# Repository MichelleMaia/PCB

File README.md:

# PCB
# PCB Layout Design

**Author:** Michelle Cavalcanti Maia  

This repository showcases a collection of PCB layout designs along with their respective circuit schematics.  
All projects were created using **KiCad** as part of the course [KiCad Like a Pro 3E](https://www.udemy.com/course/kicad-like-a-pro-3e).

## Projects
- **LED Torch** – a simple lighting circuit
- **Breadboard Power Supply** – regulated power supply for prototyping
- **Tiny Solar Power Supply** – compact solar-powered circuit
- **MCU Datalogger** – microcontroller-based data logging system

## Tools
- **KiCad** – open-source PCB design software

## About
I am passionate about embedded systems, electronics, and PCB design.  
For more projects and articles, visit my website: [michellemaia.com](https://www.michellemaia.com)

---

📅 *Last updated: September 2025*

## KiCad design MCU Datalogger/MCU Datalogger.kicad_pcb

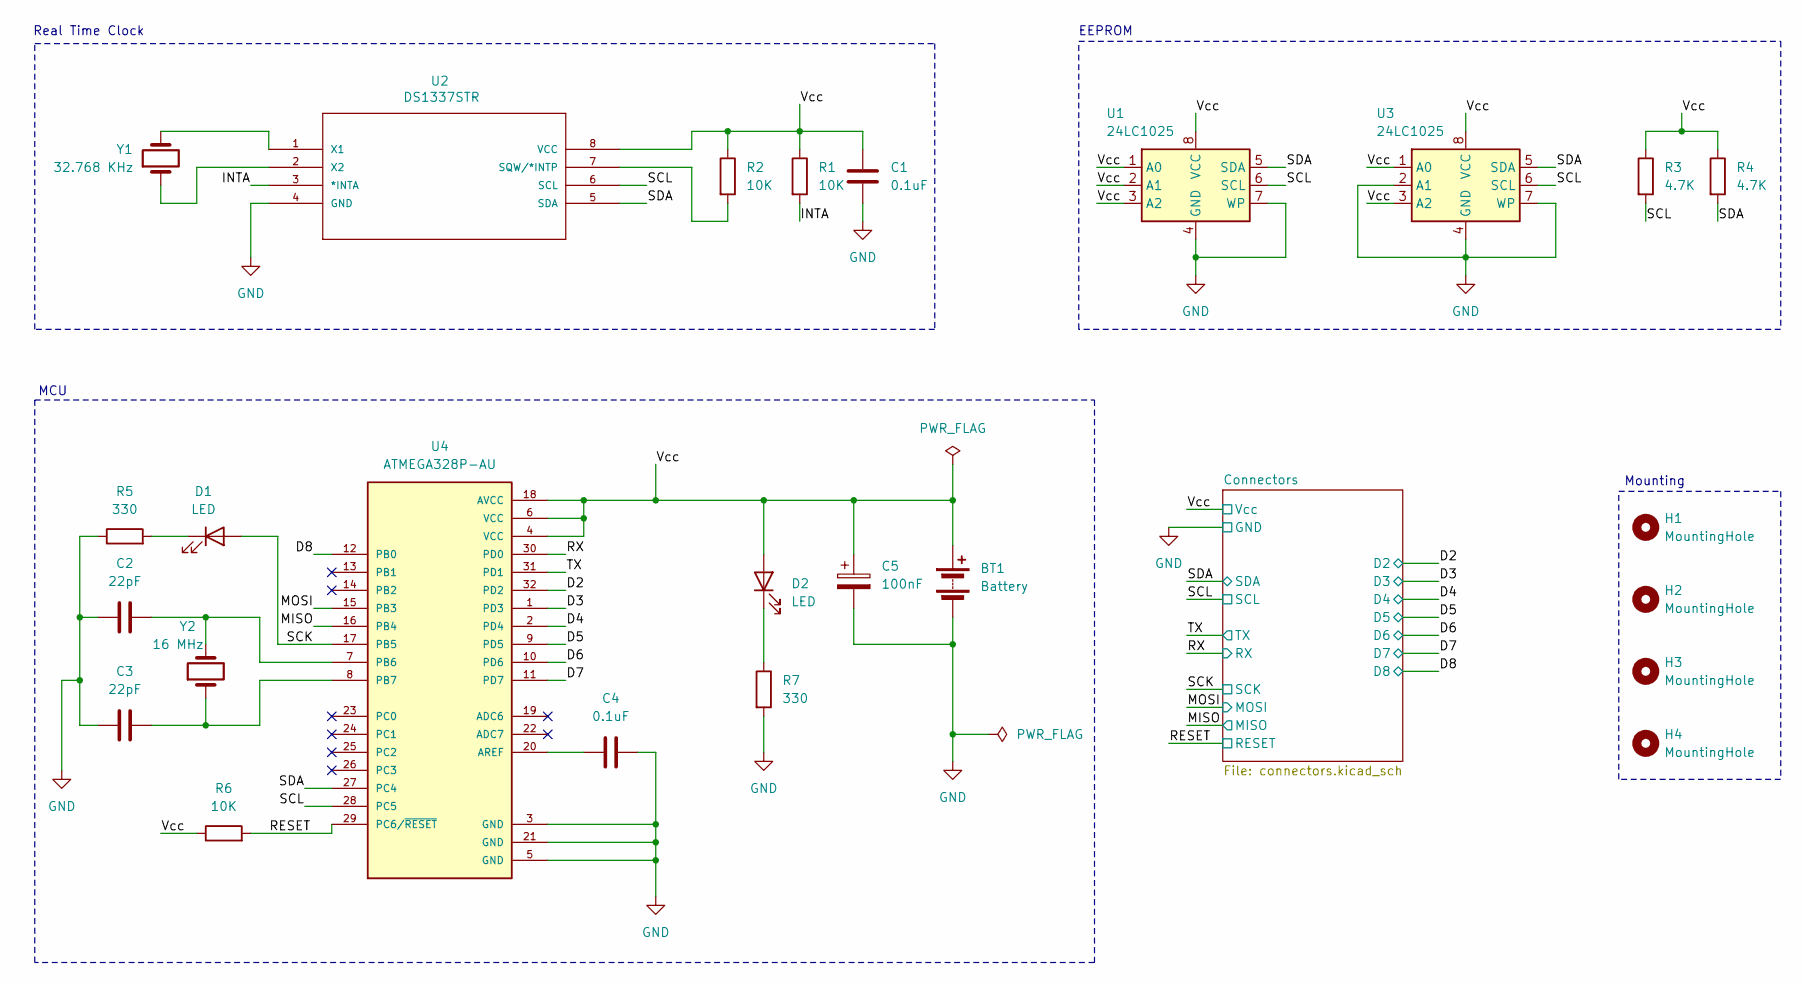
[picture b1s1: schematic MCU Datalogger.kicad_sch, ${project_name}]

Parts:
BT1: Battery; PinHeader_1x02_P2.54mm_Vertical
C1, C4: 0.1uF; C_0805_2012Metric
C2, C3: 22pF; C_0805_2012Metric
C5: 100nF; C_0805_2012Metric
D1, D2: LED; LED_0805_2012Metric
H1, H2, H3, H4: MountingHole; MountingHole_2.1mm
R1, R2, R6: 10K; R_0805_2012Metric
R3, R4: 4.7K; R_0805_2012Metric
R5, R7: 330; R_0805_2012Metric
U1, U3: 24LC1025; SOIC-8_W5.3mm
U2: DS1337STR; 21-0041B_8; MANUFACTURER_PART_NUMBER DS1337S+T&R
U4: ATMEGA328P-AU; QFP80P900X900X120-32N; PARTREV 8271A
Y1: 32.768 KHz; Crystal_SMD_5032-2Pin_5.0x3.2mm_HandSoldering
Y2: 16 MHz; Crystal_SMD_5032-2Pin_5.0x3.2mm_HandSoldering

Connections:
/D2: U4.32 (PD2); also elsewhere on the board
/D3: U4.1 (PD3); also elsewhere on the board
/D4: U4.2 (PD4); also elsewhere on the board
/D5: U4.9 (PD5); also elsewhere on the board
/D6: U4.10 (PD6); also elsewhere on the board
/D7: U4.11 (PD7); also elsewhere on the board
/D8: U4.12 (PB0); also elsewhere on the board
/INTA: R1.2, U2.3 (*INTA)
/MISO: U4.16 (PB4); also elsewhere on the board
/MOSI: U4.15 (PB3); also elsewhere on the board
/RESET: R6.2, U4.29 (PC6/~RESET); also elsewhere on the board
/RX: U4.30 (PD0); also elsewhere on the board
/SCK: D1.2 (A), U4.17 (PB5); also elsewhere on the board
/SCL: R3.2, U1.6 (SCL), U2.6 (SCL), U3.6 (SCL), U4.28 (PC5); also elsewhere on the board
/SDA: R4.2, U1.5 (SDA), U2.5 (SDA), U3.5 (SDA), U4.27 (PC4); also elsewhere on the board
/TX: U4.31 (PD1); also elsewhere on the board
/Vcc: BT1.1 (+), C1.1, C5.1, D2.2 (A), R1.1, R2.1, R3.1, R4.1, R6.1, U1.1 (A0), U1.2 (A1), U1.3 (A2), U1.8 (VCC), U2.8 (VCC), U3.1 (A0), U3.3 (A2), U3.8 (VCC), U4.4 (VCC), U4.6 (VCC), U4.18 (AVCC); also elsewhere on the board
GND: BT1.2 (-), C1.2, C2.1, C3.1, C4.2, C5.2, R5.1, R7.2, U1.4 (GND), U1.7 (WP), U2.4 (GND), U3.2 (A1), U3.4 (GND), U3.7 (WP), U4.3 (GND), U4.5 (GND), U4.21 (GND); also elsewhere on the board
unnamed: D1.1 (K), R5.2
unnamed: D2.1 (K), R7.1
unnamed: R2.2, U2.7 (SQW/*INTP)
unnamed: U2.1 (X1), Y1.2
unnamed: U2.2 (X2), Y1.1
unnamed: C4.1, U4.20 (AREF)
unnamed: C2.2, U4.7 (PB6), Y2.2
unnamed: C3.2, U4.8 (PB7), Y2.1

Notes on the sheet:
Real Time Clock
Mounting
EEPROM
MCU

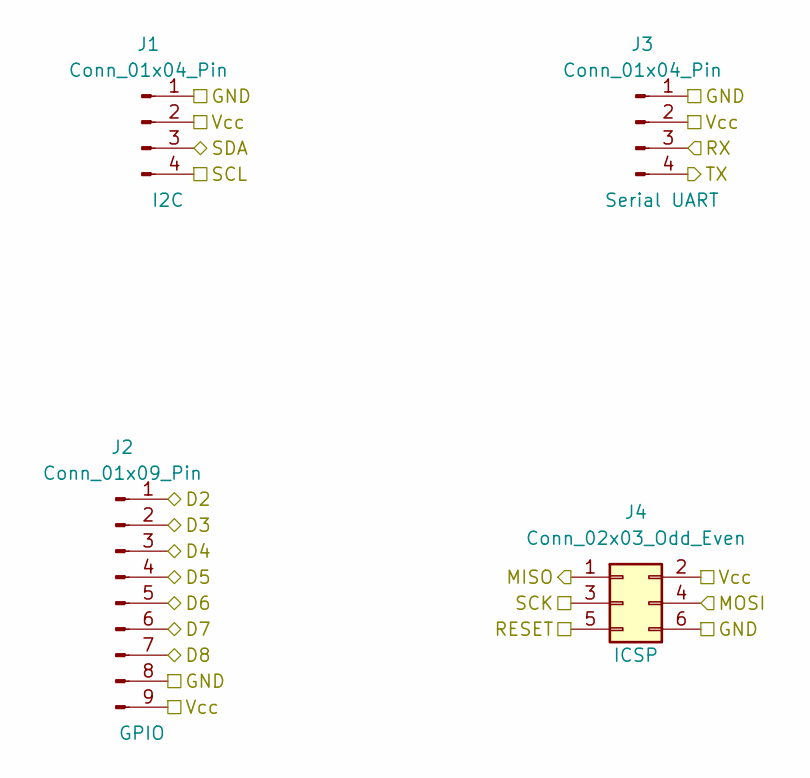
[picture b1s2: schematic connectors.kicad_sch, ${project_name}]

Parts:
J1, J3: Conn_01x04_Pin; PinHeader_1x04_P2.54mm_Vertical
J2: Conn_01x09_Pin; PinHeader_1x09_P2.54mm_Vertical
J4: Conn_02x03_Odd_Even; PinHeader_2x03_P2.54mm_Vertical

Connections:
/D2: J2.1; also elsewhere on the board
/D3: J2.2; also elsewhere on the board
/D4: J2.3; also elsewhere on the board
/D5: J2.4; also elsewhere on the board
/D6: J2.5; also elsewhere on the board
/D7: J2.6; also elsewhere on the board
/D8: J2.7; also elsewhere on the board
/MISO: J4.1; also elsewhere on the board
/MOSI: J4.4; also elsewhere on the board
/RESET: J4.5; also elsewhere on the board
/RX: J3.3; also elsewhere on the board
/SCK: J4.3; also elsewhere on the board
/SCL: J1.4; also elsewhere on the board
/SDA: J1.3; also elsewhere on the board
/TX: J3.4; also elsewhere on the board
/Vcc: J1.2, J2.9, J3.2, J4.2; also elsewhere on the board
GND: J1.1, J2.8, J3.1, J4.6; also elsewhere on the board

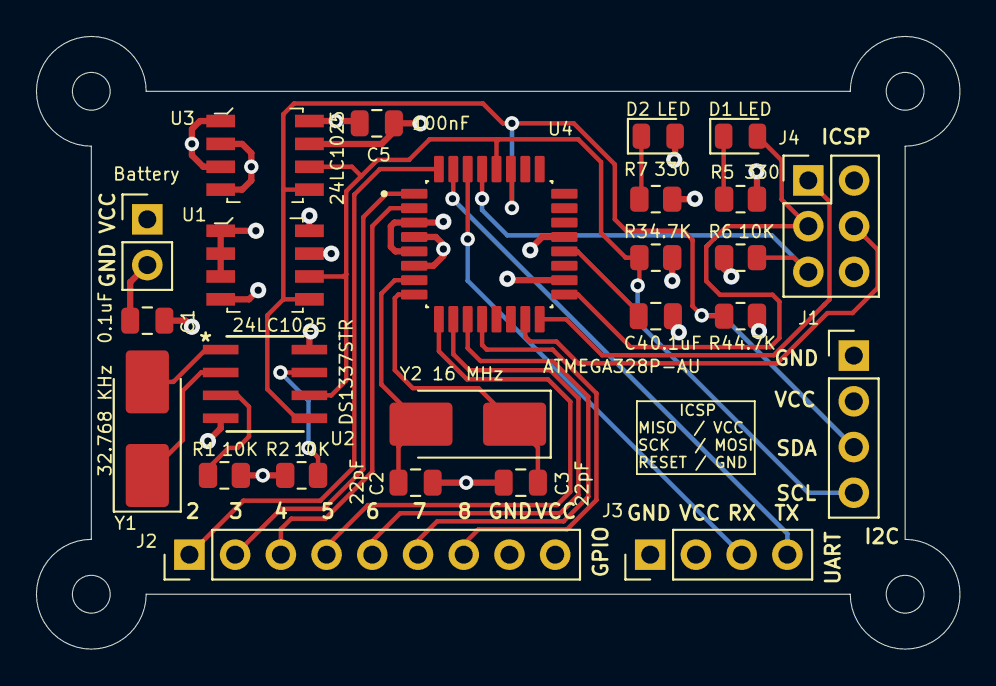
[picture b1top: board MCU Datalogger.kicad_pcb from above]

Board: 4 copper layers, 51.3 x 34.0 mm, 29 parts (0 on the bottom side), 26 nets.

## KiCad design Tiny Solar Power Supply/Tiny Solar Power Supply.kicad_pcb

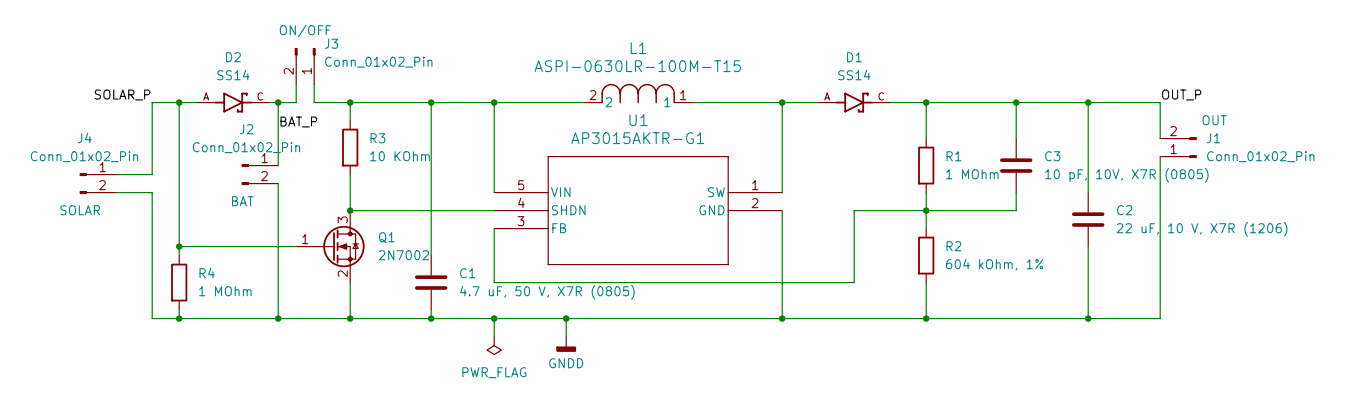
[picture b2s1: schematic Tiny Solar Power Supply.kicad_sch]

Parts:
C1: 4.7 uF, 50 V, X7R (0805); C_0805_2012Metric
C2: 22 uF, 10 V, X7R (1206); C_1206_3216Metric
C3: 10 pF, 10V, X7R (0805); C_0805_2012Metric
D1, D2: SS14; DIOM4325X250N; PARTREV O2102
J1, J2, J3: Conn_01x02_Pin; PinHeader_1x02_P2.54mm_Vertical
J4: Conn_01x02_Pin; PinHeader_1x02_P2.54mm_Horizontal
L1: ASPI-0630LR-100M-T15; IND_ASPI-0630LR_ABR
Q1: 2N7002; SOT-23
R1, R4: 1 MOhm; R_0805_2012Metric
R2: 604 kOhm, 1%; R_0805_2012Metric
R3: 10 KOhm; R_0805_2012Metric
U1: AP3015AKTR-G1; SOT23-5_1P55X2P9_DIO

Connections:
/BAT_P: D2.C, J2.1, J3.2
/OUT_P: C2.1, C3.1, D1.C, J1.2, R1.1
/SOLAR_P: D2.A, J4.1, Q1.1 (G), R4.1
GNDD: C1.2, C2.2, J1.1, J2.2, J4.2, Q1.2 (S), R2.2, R4.2, U1.2 (GND)
unnamed: C1.1, J3.1, L1.2, R3.1, U1.5 (VIN)
unnamed: Q1.3 (D), R3.2, U1.4 (SHDN)
unnamed: C3.2, R1.2, R2.1, U1.3 (FB)
unnamed: D1.A, L1.1, U1.1 (SW)

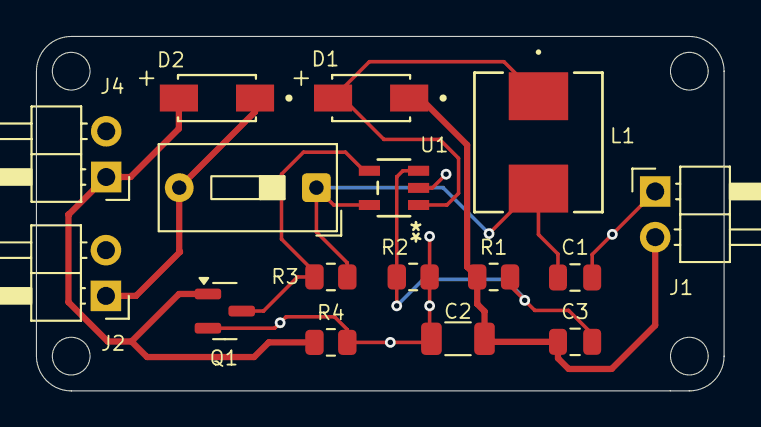
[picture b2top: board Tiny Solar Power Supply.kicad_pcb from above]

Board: 2 copper layers, 38.2 x 19.7 mm, 16 parts (0 on the bottom side), 8 nets.

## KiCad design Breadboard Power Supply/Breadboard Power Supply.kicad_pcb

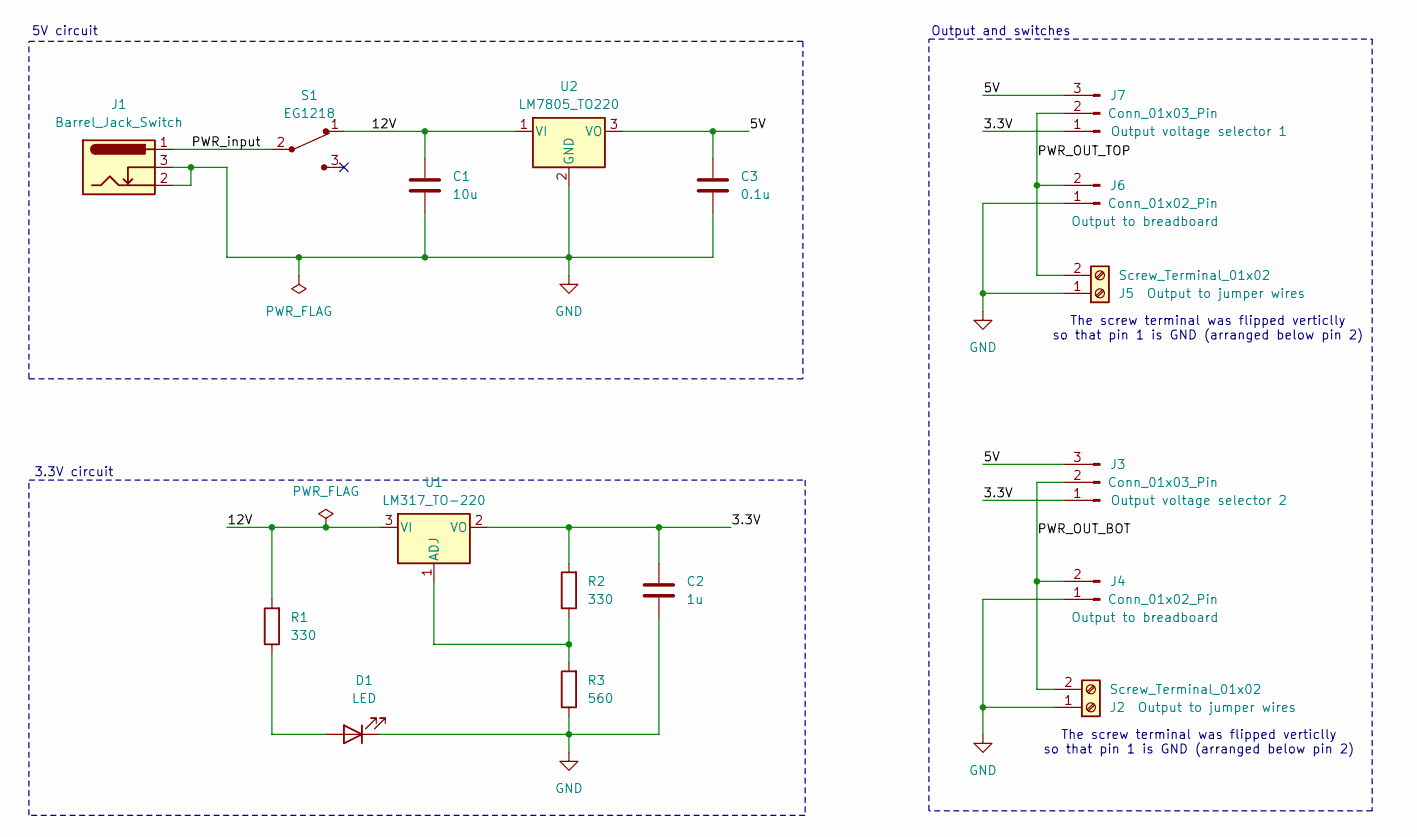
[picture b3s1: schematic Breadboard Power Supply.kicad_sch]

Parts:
C1: 10u; C_Disc_D3.0mm_W1.6mm_P2.50mm
C2: 1u; C_Disc_D3.0mm_W1.6mm_P2.50mm
C3: 0.1u; C_Disc_D3.0mm_W1.6mm_P2.50mm
D1: LED; LED_D5.0mm
J1: Barrel_Jack_Switch; BarrelJack_Horizontal
J2, J5: Screw_Terminal_01x02; TerminalBlock_bornier-2_P5.08mm
J3, J7: Conn_01x03_Pin; PinHeader_1x03_P2.54mm_Vertical
J4, J6: Conn_01x02_Pin; PinHeader_1x02_P2.54mm_Vertical
R1, R2: 330; R_Axial_DIN0204_L3.6mm_D1.6mm_P7.62mm_Horizontal
R3: 560; R_Axial_DIN0204_L3.6mm_D1.6mm_P7.62mm_Horizontal
S1: EG1218; Switch_Slide_11.6x4mm_EG1218; MPN EG1218; Digi-Key_PN EG1903-ND
U1: LM317_TO-220; TO-220-3_Vertical
U2: LM7805_TO220; TO-220-3_Vertical

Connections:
/3.3V: C2.1, J3.1, J7.1, R2.2, U1.2 (VO)
/5V: C3.1, J3.3, J7.3, U2.3 (VO)
/12V: C1.1, R1.2, S1.1, U1.3 (VI), U2.1 (VI)
/PWR_OUT_BOT: J2.2, J3.2, J4.2
/PWR_OUT_TOP: J5.2, J6.2, J7.2
/PWR_input: J1.1, S1.2
GND: C1.2, C2.2, C3.2, D1.1 (K), J1.2, J1.3, J2.1, J4.1, J5.1, J6.1, R3.1, U2.2 (GND)
unnamed: D1.2 (A), R1.1
unnamed: R2.1, R3.2, U1.1 (ADJ)

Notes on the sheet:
3.3V circuit
5V circuit
Output and switches
The screw terminal was flipped verticlly so that pin 1 is GND (arranged below pin 2)

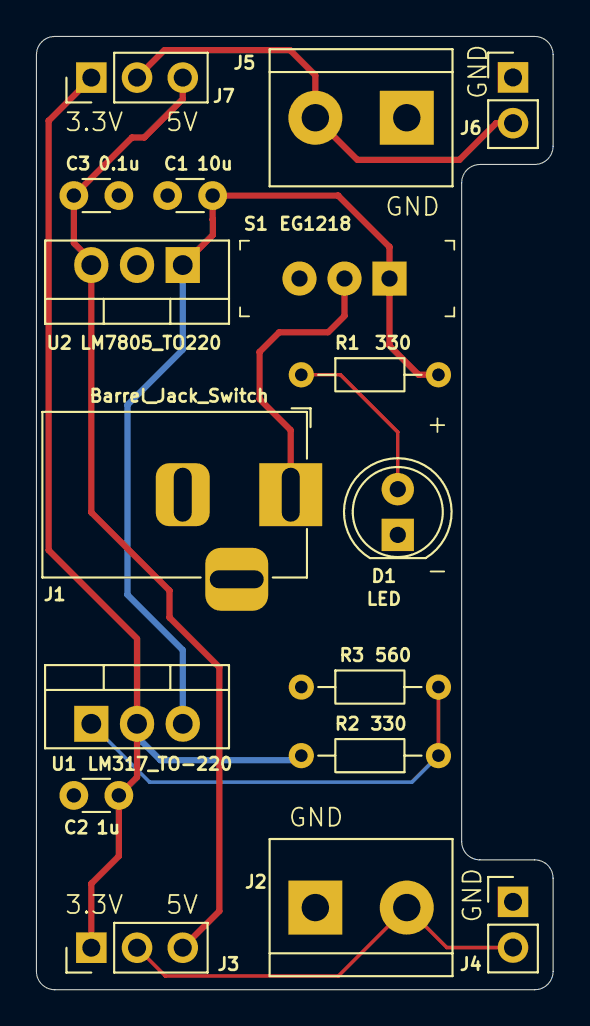
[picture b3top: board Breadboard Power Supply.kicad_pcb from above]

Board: 2 copper layers, 28.7 x 53.0 mm, 17 parts (0 on the bottom side), 9 nets.

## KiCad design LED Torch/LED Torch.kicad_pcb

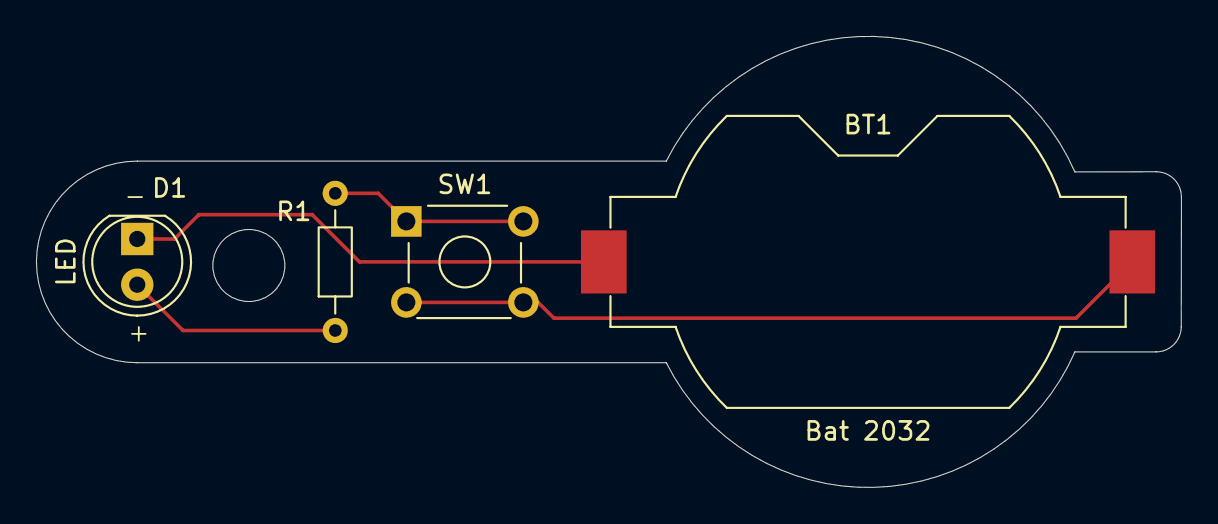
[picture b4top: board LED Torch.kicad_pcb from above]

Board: 2 copper layers, 63.6 x 25.1 mm, 4 parts (0 on the bottom side), 4 nets.

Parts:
BT1: Bat 2032; BatteryHolder_Keystone_1058_1x2032
D1: LED; LED_D5.0mm
R1: R; R_Axial_DIN0204_L3.6mm_D1.6mm_P7.62mm_Horizontal
SW1: SW_DPDT_x2; SW_TH_Tactile_Omron_B3F-10xx

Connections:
/LED_anode: D1.2 (A), R1.1
/LED_cathode: BT1.2 (-), D1.1 (K)
/bat_pos: BT1.1 (+), SW1.2 (B)
unnamed: R1.2, SW1.1 (A)

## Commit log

2025-09-03 Update README.md
    Adding projects descriptions
2025-09-03 LED Torch - adding project files
2025-09-04 .gitignore - adding .lck autosave files
2025-09-04 Breadboard Power Supply - adding project files
2025-09-04 Tiny Solar Power Supply - adding project files
2025-09-04 MCU Datalogger - adding files
